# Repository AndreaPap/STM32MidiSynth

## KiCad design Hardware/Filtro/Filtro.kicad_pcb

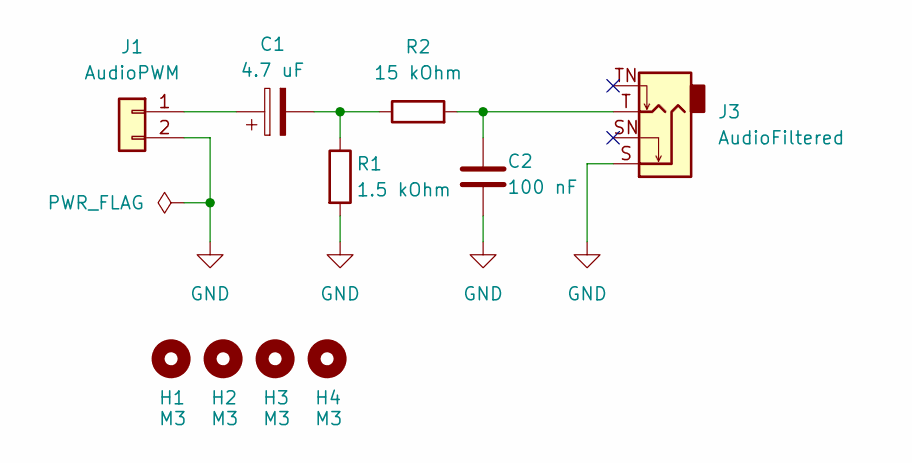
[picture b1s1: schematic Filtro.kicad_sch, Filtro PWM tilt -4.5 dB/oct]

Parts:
C1: 4.7 uF; CP_Radial_D4.0mm_P1.50mm
C2: 100 nF; C_Disc_D5.0mm_W2.5mm_P5.00mm
H1, H2, H3, H4: M3; MountingHole_3.2mm_M3
J1: AudioPWM; TerminalBlock_Phoenix_MPT-0,5-2-2.54_1x02_P2.54mm_Horizontal
J3: AudioFiltered; Jack_6.35mm_Neutrik_NMJ4HCD2_Horizontal
R1: 1.5 kOhm; R_Axial_DIN0207_L6.3mm_D2.5mm_P7.62mm_Horizontal
R2: 15 kOhm; R_Axial_DIN0207_L6.3mm_D2.5mm_P7.62mm_Horizontal

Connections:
GND: C2.2, J1.2, J3.S, R1.2
unnamed: C1.2, R1.1, R2.1
unnamed: C2.1, J3.T, R2.2
unnamed: C1.1, J1.1

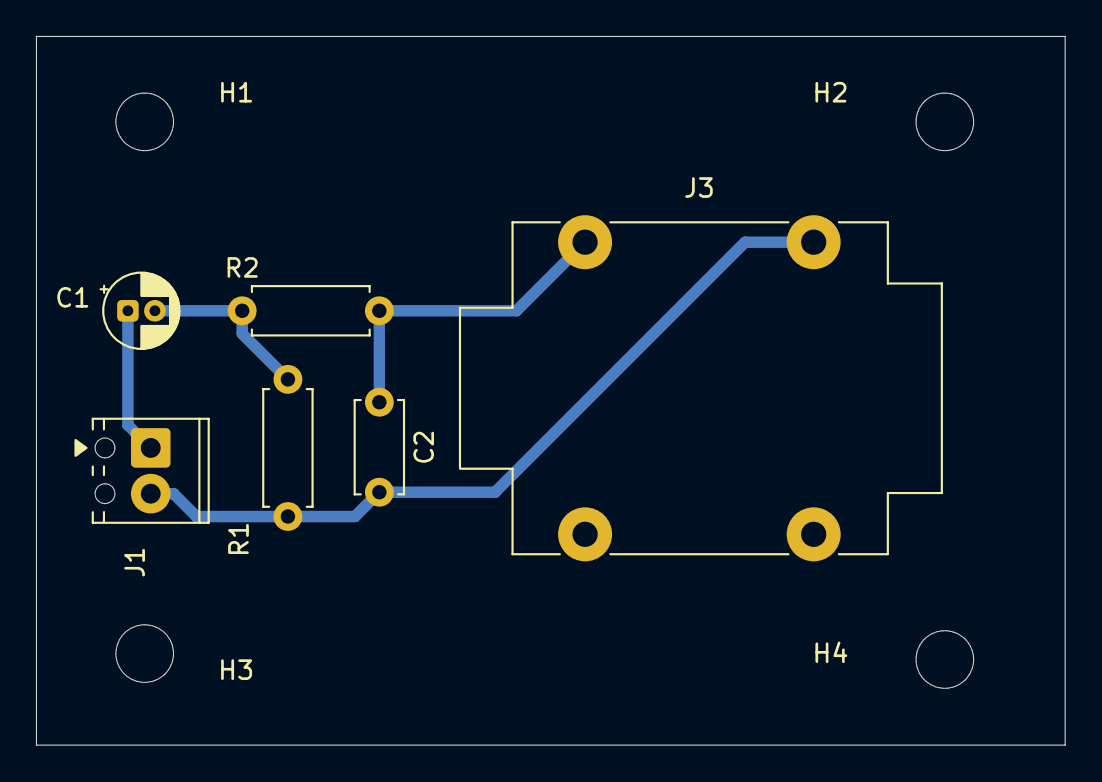
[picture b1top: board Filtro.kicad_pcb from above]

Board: 2 copper layers, 57.1 x 39.4 mm, 10 parts (0 on the bottom side), 4 nets.
